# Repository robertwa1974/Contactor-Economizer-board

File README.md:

# Contactor Economizer

A two-channel 12 V economizer board for high-voltage contactor coils, built for an EV conversion using
salvaged contactors.

When the vehicle controller commands a contactor closed, the board pulls it in with a strong,
current-regulated pulse and then holds it at a much lower current. For a Gigavac GV200-005 that cuts the
12 V load from about 28 W to under 1 W per contactor, and the coil runs cool.

**Status:** revision B. The design is complete and the files are ready for JLCPCB, but no board has
been built or tested yet.

## Documentation

- **[Operator's manual](OPERATORS_MANUAL.md)** covers fitting the connectors, wiring, programming, setup,
  bench testing, installation, fault codes and serial commands.
- [Design notes](handoff.md) record the design decisions, calculations, reviews and open items.

## Features

- Two independent channels, commanded directly by the VCU's existing low-side contactor outputs. No VCU
  firmware change is needed.
- Pick-up and hold currents are both regulated, so one board suits coils from 0.5 to 100 Ω.
- Built-in presets for the Gigavac GV200-005, LS Electric GER150 and Panasonic AEV14012. Custom
  settings are entered over a serial port.
- Fail-safe:
  - Only the VCU command can switch a coil on; the microcontroller can only force it off.
  - With no firmware running, the contactors stay open.
- Fast release from a hardware clamp, reverse-polarity protection, and an open-drain status output per
  channel.
- STM32G031 microcontroller, TI TPS1H100-Q1 smart high-side switches, and INA240 current sensing.
- Optional stacking socket for an insulation monitor (IMD) board. The IMD can block a contactor from
  closing but never forces one open. Without an IMD, the board works stand-alone.
- 76 × 66 mm, 2-layer board.

## Repository layout

| Path | Contents |
|---|---|
| `src/main.cpp`, `platformio.ini` | Firmware (PlatformIO, STM32duino) |
| `hw/econ.kicad_pro` | KiCad 10 project: open this to view the schematic and board |
| `hw/econ_schematic.pdf` | Schematic as a PDF |
| `hw/fab/` | JLCPCB order files: Gerber zip, BOM, placement file, 3D renders |
| `hw/design.py` | Parts and connections. The schematic and board are generated from this file. |
| `hw/gen_*.py`, `hw/fab.py` | Generator scripts (see the design notes for the pipeline) |

The schematic and board are generated from `hw/design.py`. Change that file and regenerate, rather
than editing the KiCad files by hand.

## Building the firmware

Open the repository in VS Code with the PlatformIO extension and click **Build**, or run `pio run`.
Flashing and setup are covered in the [operator's manual](OPERATORS_MANUAL.md#5-programming-the-board).

## License

[MIT](LICENSE): this covers the firmware, the hardware design files and the documentation. The board
switches circuits on high-voltage systems. Build and use it at your own risk; the license provides no
warranty.

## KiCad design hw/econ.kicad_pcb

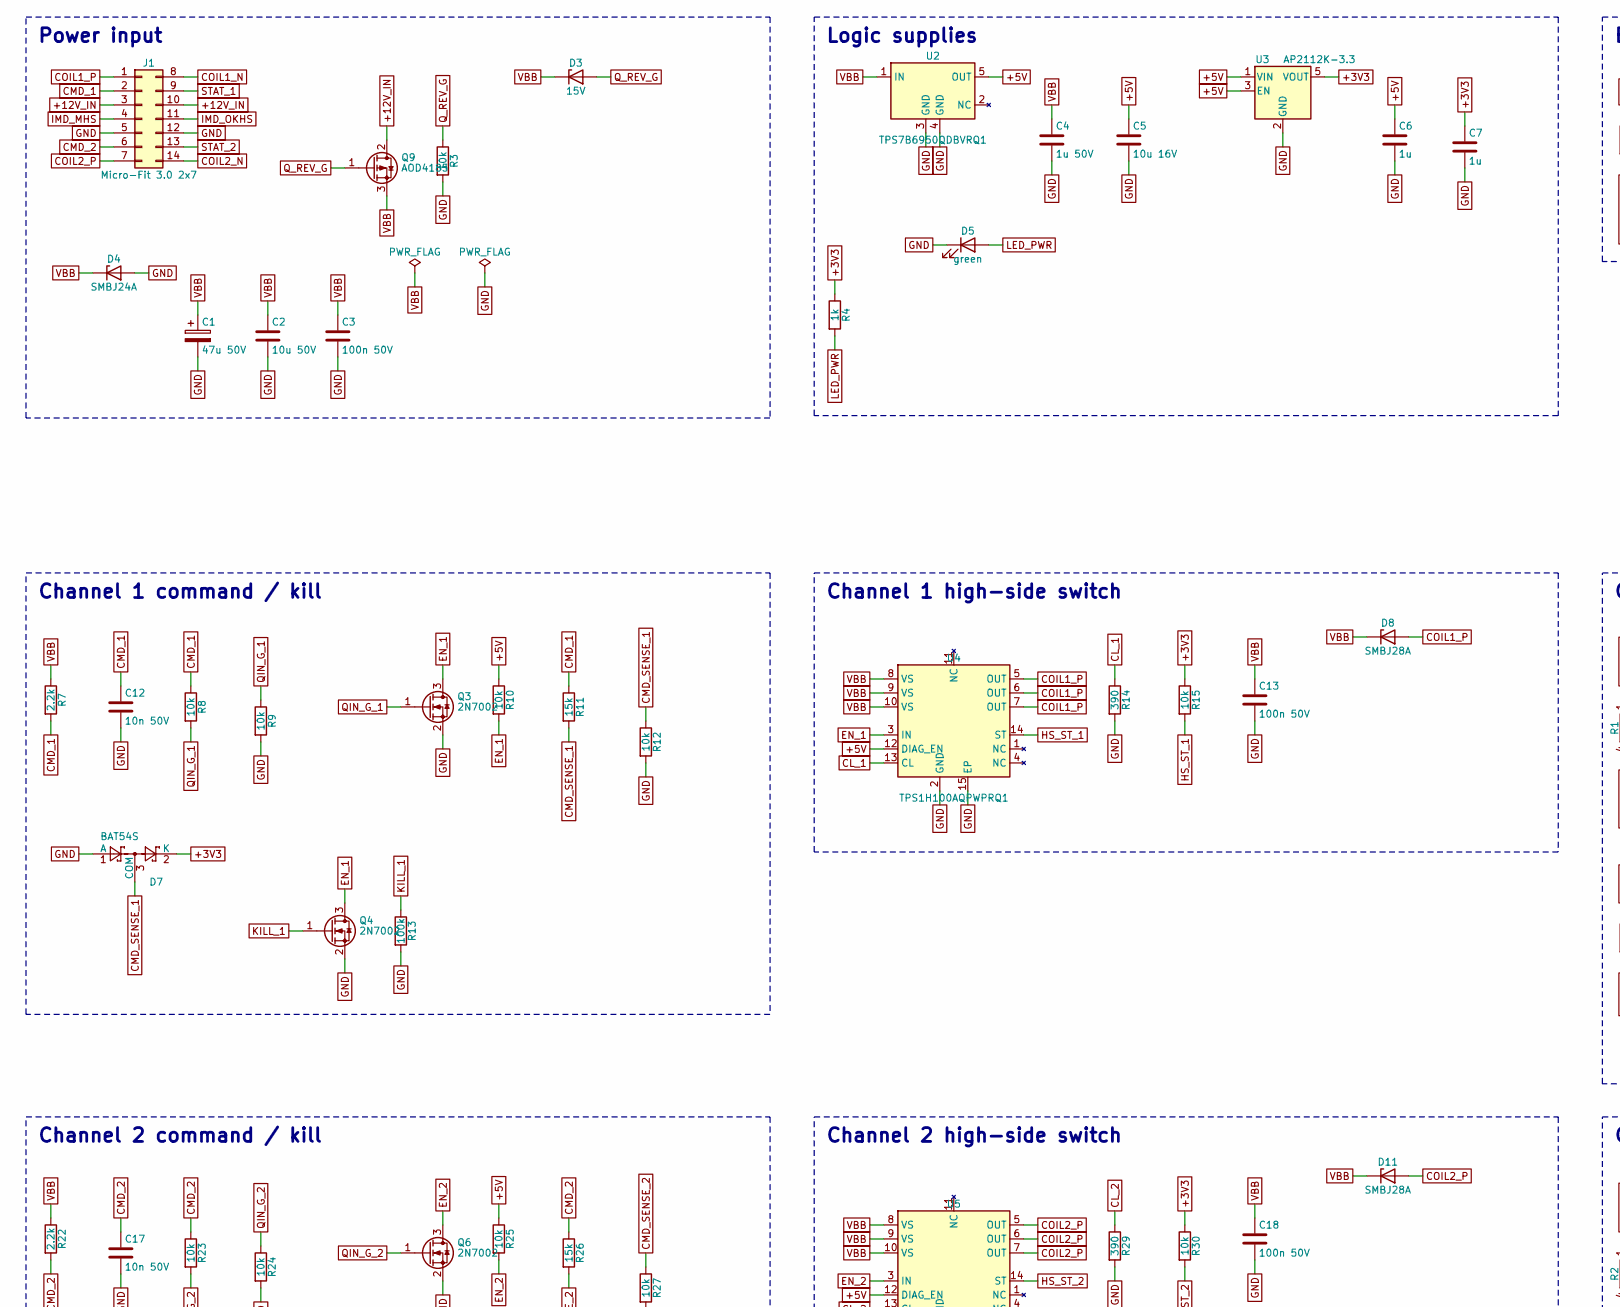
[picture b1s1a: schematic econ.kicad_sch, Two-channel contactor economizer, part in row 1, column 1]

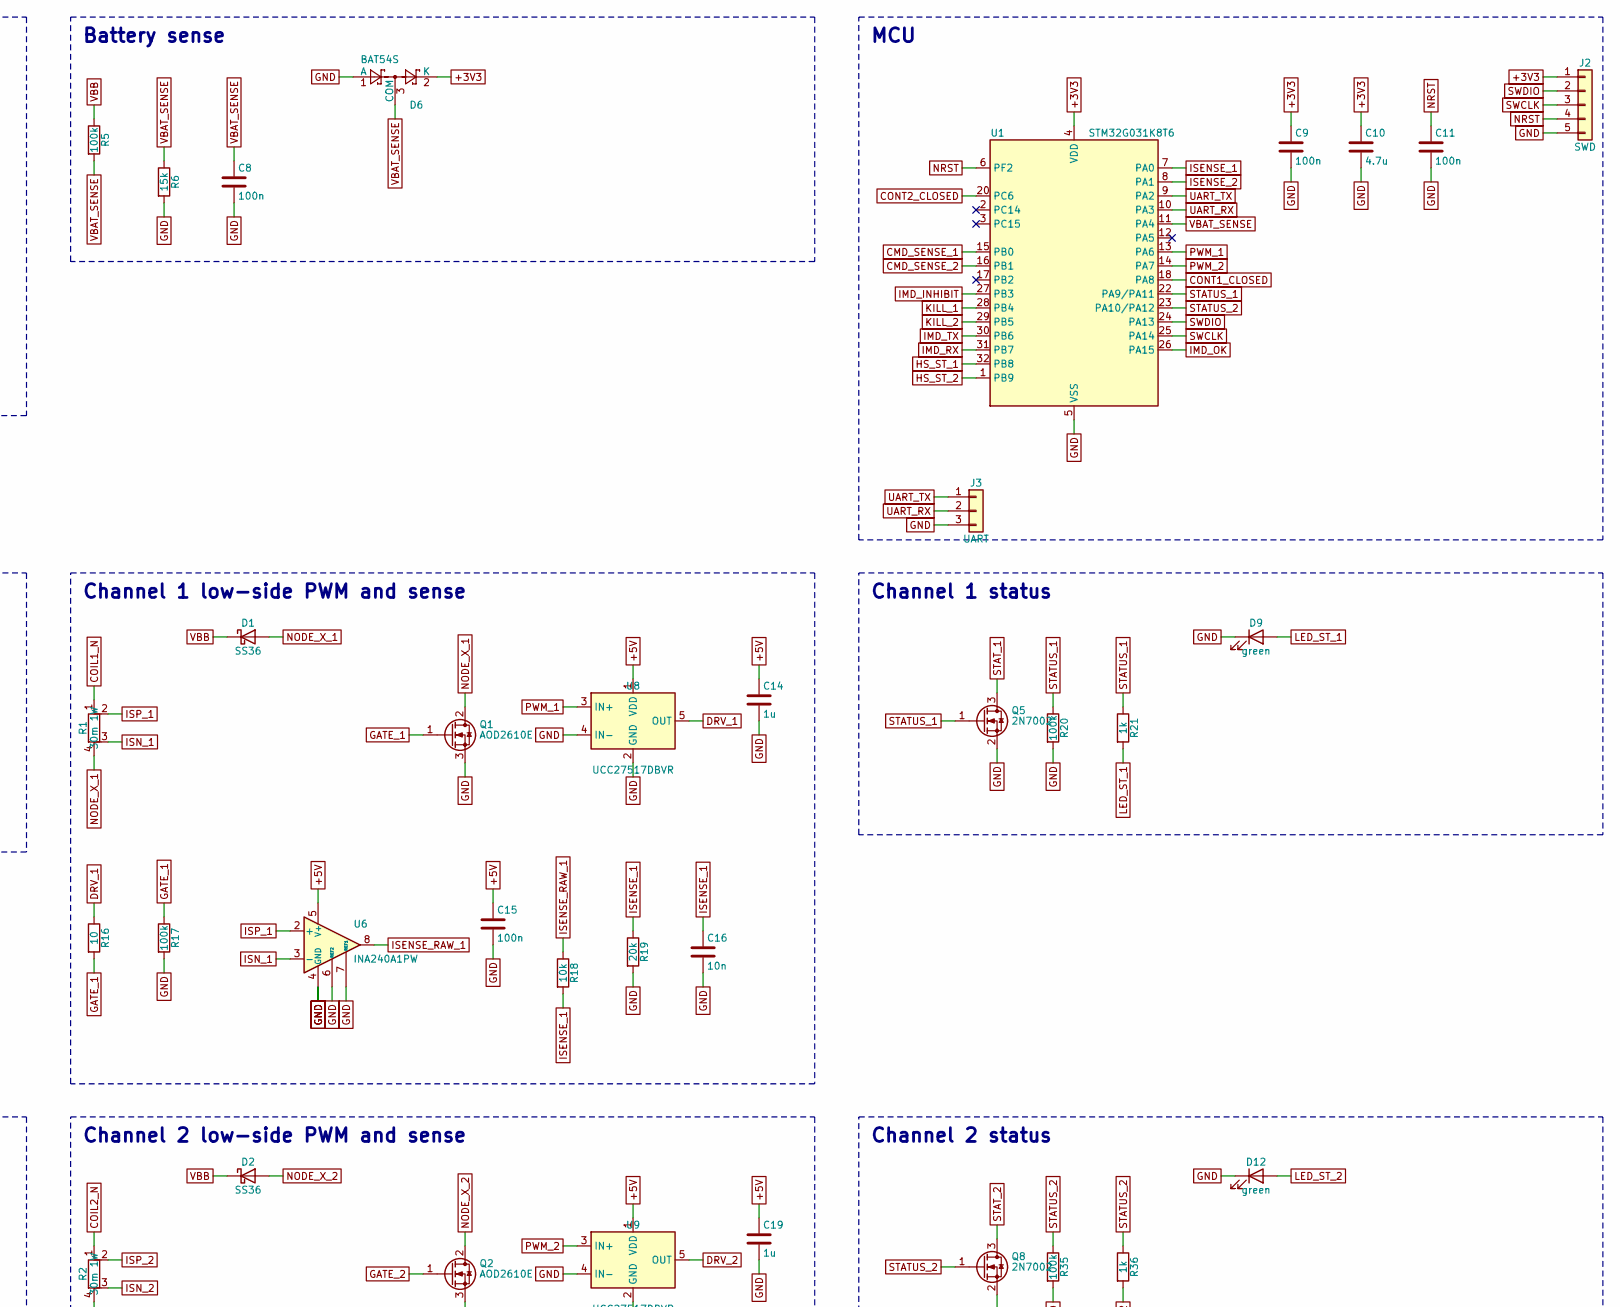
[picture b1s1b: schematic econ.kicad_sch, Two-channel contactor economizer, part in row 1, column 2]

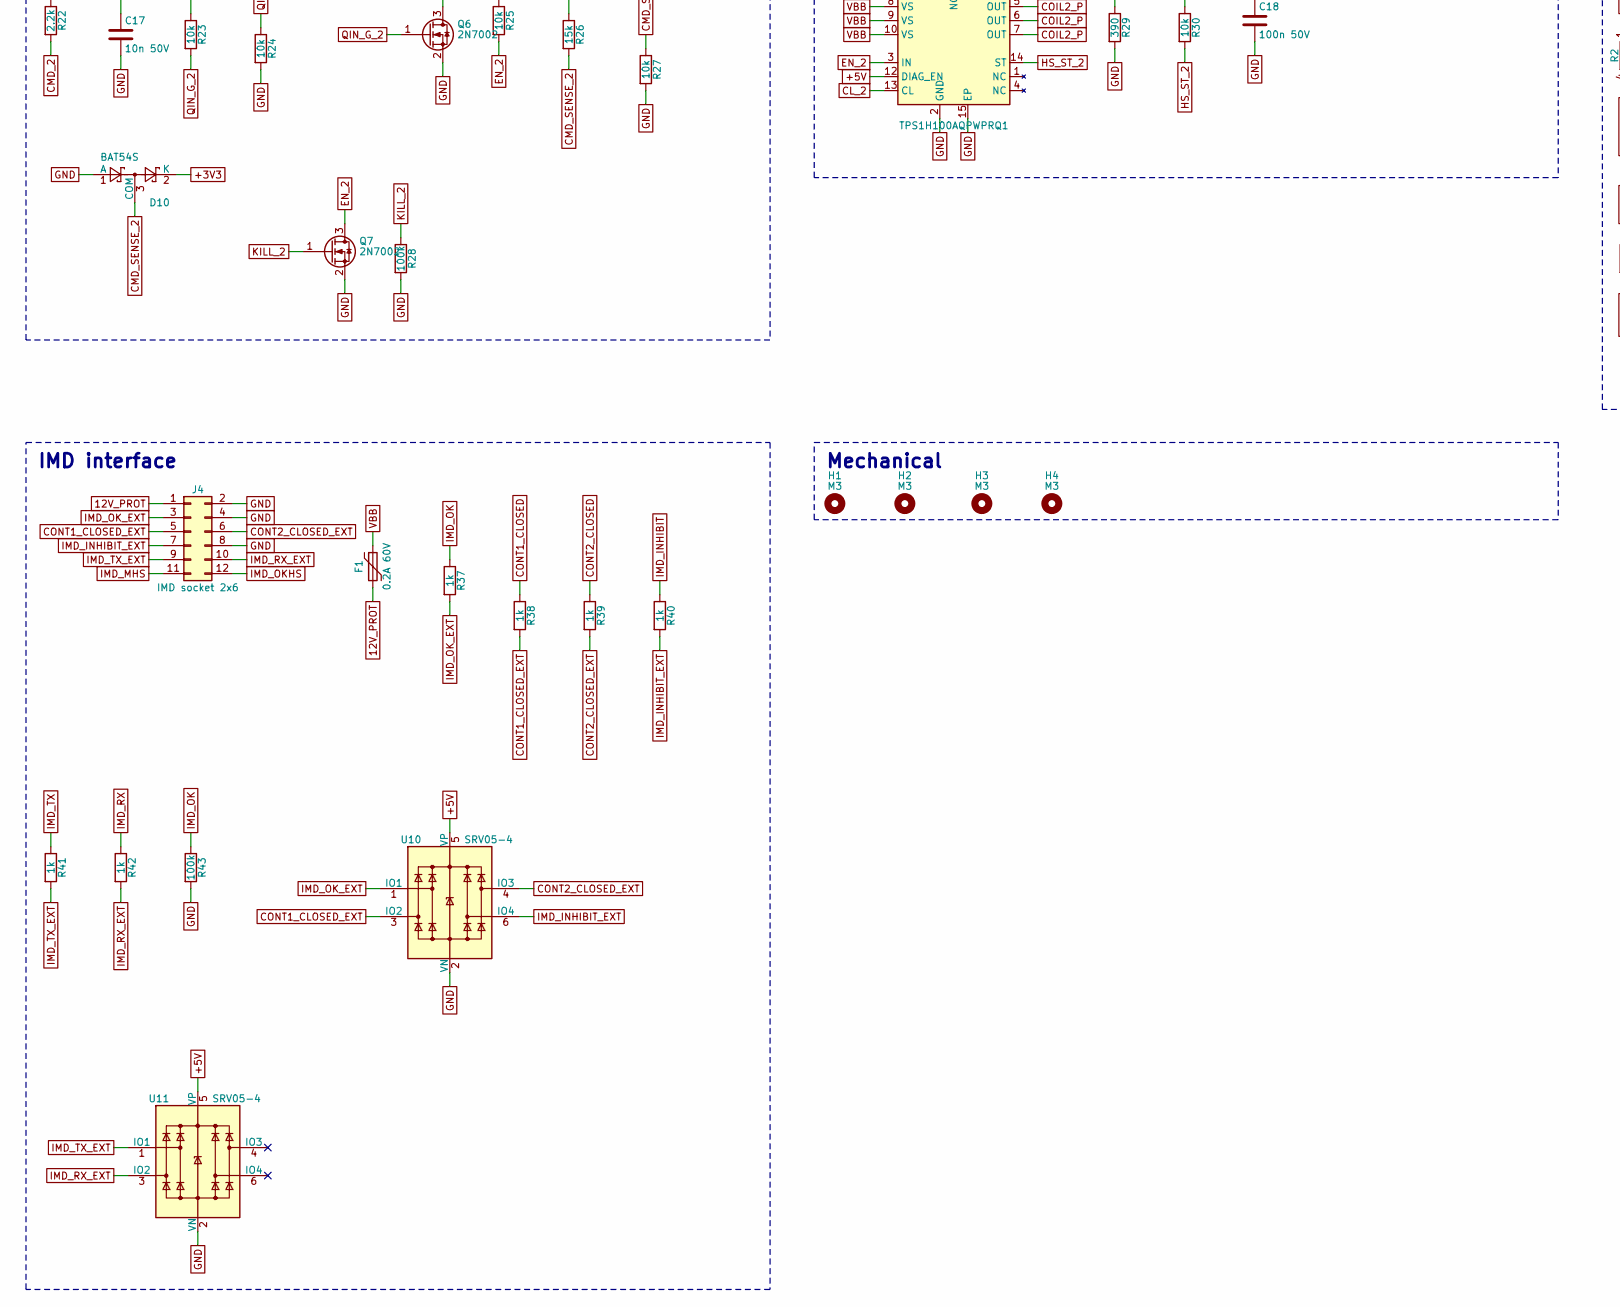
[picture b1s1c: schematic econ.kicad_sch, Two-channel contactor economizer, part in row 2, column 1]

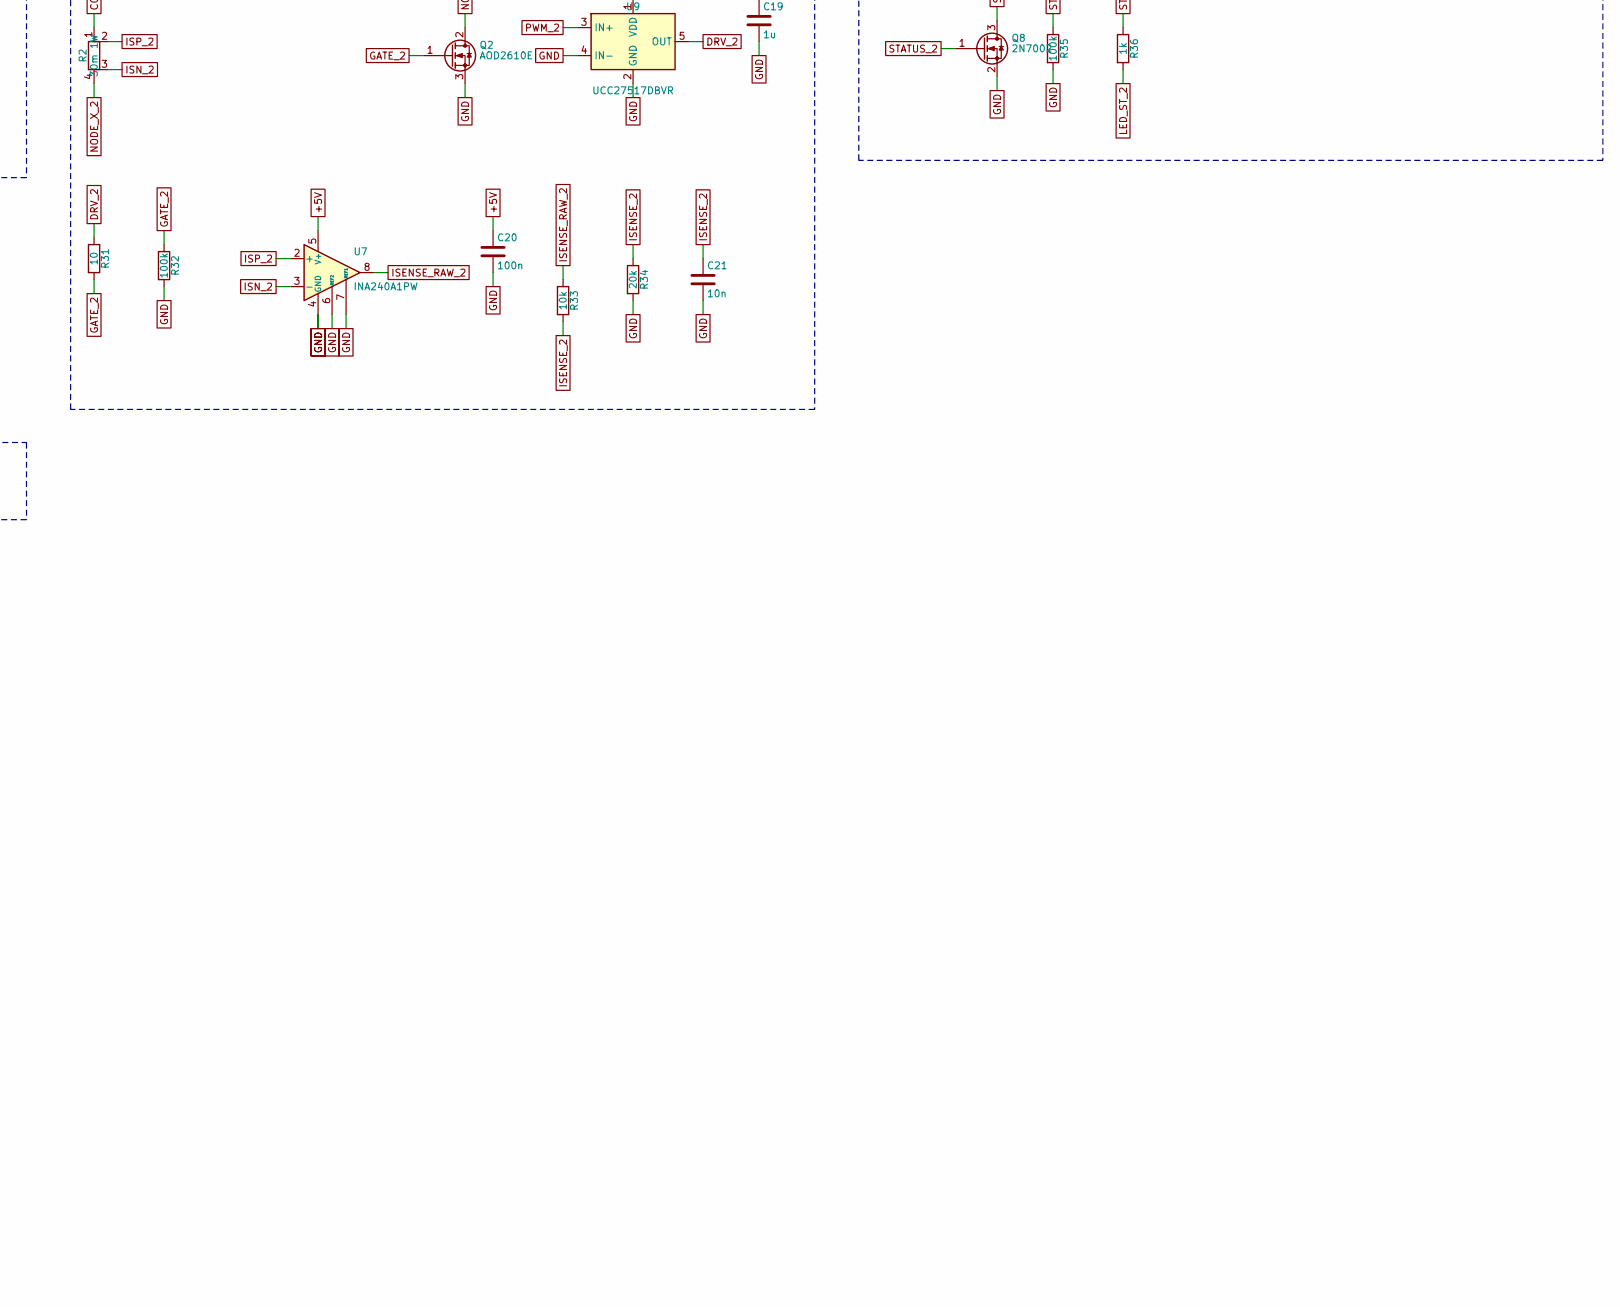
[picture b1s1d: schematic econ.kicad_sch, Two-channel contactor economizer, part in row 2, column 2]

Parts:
C1: 47u 50V; CP_Elec_6.3x7.7
C2: 10u 50V; C_1206_3216Metric
C3, C13, C18: 100n 50V; C_0603_1608Metric
C4: 1u 50V; C_0805_2012Metric
C5: 10u 16V; C_0805_2012Metric
C6, C7, C14, C19: 1u; C_0603_1608Metric
C8, C9, C11, C15, C20: 100n; C_0603_1608Metric
C10: 4.7u; C_0603_1608Metric
C12, C17: 10n 50V; C_0603_1608Metric
C16, C21: 10n; C_0603_1608Metric
D1, D2: SS36; D_SMA; MPN SS36; LCSC C727061
D3: 15V; D_SOD-123; MPN MMSZ5245B (15 V)
D4: SMBJ24A; D_SMB; MPN SMBJ24A; LCSC C224017
D5, D9, D12: green; LED_0603_1608Metric
D6, D7, D10: BAT54S; SOT-23; MPN BAT54S; LCSC C171786
D8, D11: SMBJ28A; D_SMB; MPN SMBJ28A
F1: 0.2A 60V; Fuse_1812_4532Metric; MPN MF-MSMF020/60
H1, H2, H3, H4: M3; MountingHole_3.2mm_M3
J1: Micro-Fit 3.0 2x7; Molex_Micro-Fit_3.0_43045-1400_2x07_P3.00mm_Horizontal; MPN Molex 43045-1400
J2: SWD; PinHeader_1x05_P2.54mm_Horizontal_Edge
J3: UART; PinHeader_1x03_P2.54mm_Horizontal_Edge
J4: IMD socket 2x6; PinSocket_2x06_P2.54mm_Vertical; MPN 2x6 female socket, 2.54 mm, 8.5 mm tall
Q1, Q2: AOD2610E; TO-252-2; MPN AOD2610E; LCSC C282428
Q3, Q4, Q5, Q6, Q7, Q8: 2N7002; SOT-23; MPN 2N7002; LCSC C8545
Q9: AOD4185; TO-252-2; MPN AOD4185; LCSC C400894
R1, R2: 30m 1W; R_2512_Kelvin; MPN RLP25FECR030; LCSC C2930482
R3, R8, R9, R10, R12, R15, R18, R23, R24, R25, R27, R30, R33: 10k; R_0603_1608Metric
R4, R21, R36, R37, R38, R39, R40, R41, R42: 1k; R_0603_1608Metric
R5, R13, R17, R20, R28, R32, R35, R43: 100k; R_0603_1608Metric
R6, R11, R26: 15k; R_0603_1608Metric
R7, R22: 2.2k; R_1206_3216Metric
R14, R29: 390; R_0603_1608Metric
R16, R31: 10; R_0603_1608Metric
R19, R34: 20k; R_0603_1608Metric
U1: STM32G031K8T6; LQFP-32_7x7mm_P0.8mm; MPN STM32G031K8T6; LCSC C432203
U2: TPS7B6950QDBVRQ1; SOT-23-5; MPN TPS7B6950QDBVRQ1; LCSC C132202
U3: AP2112K-3.3; SOT-23-5; MPN AP2112K-3.3TRG1; LCSC C51118
U4, U5: TPS1H100AQPWPRQ1; Texas_HTSSOP-14-1EP_4.4x5mm_P0.65mm_EP3.4x5mm_Mask3.155x3.2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; MPN TPS1H100AQPWPRQ1; LCSC C478465
U6, U7: INA240A1PW; TSSOP-8_4.4x3mm_P0.65mm; MPN INA240A1PWR; LCSC C93965
U8, U9: UCC27517DBVR; SOT-23-5; MPN UCC27517DBVR; LCSC C99395
U10, U11: SRV05-4; SOT-23-6; MPN SRV05-4

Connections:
12V_PROT: F1.2, J4.1
+3V3: C7.1, C9.1, C10.1, D6.2 (K), D7.2 (K), D10.2 (K), J2.1, R4.1, R15.1, R30.1, U1.4 (VDD), U3.5 (VOUT)
+5V: C5.1, C6.1, C14.1, C15.1, C19.1, C20.1, R10.1, R25.1, U2.5 (OUT), U3.1 (VIN), U3.3 (EN), U4.12 (DIAG_EN), U5.12 (DIAG_EN), U6.5 (V+), U7.5 (V+), U8.1 (VDD), U9.1 (VDD), U10.5 (VP), U11.5 (VP)
+12V_IN: J1.3, J1.10, Q9.2 (D)
CL_1: R14.1, U4.13 (CL)
CL_2: R29.1, U5.13 (CL)
CMD_1: C12.1, J1.2, R7.2, R8.1, R11.1
CMD_2: C17.1, J1.6, R22.2, R23.1, R26.1
CMD_SENSE_1: D7.3 (COM), R11.2, R12.1, U1.15 (PB0)
CMD_SENSE_2: D10.3 (COM), R26.2, R27.1, U1.16 (PB1)
COIL1_N: J1.8, R1.1
COIL1_P: D8.2 (A), J1.1, U4.5 (OUT), U4.6 (OUT), U4.7 (OUT)
COIL2_N: J1.14, R2.1
COIL2_P: D11.2 (A), J1.7, U5.5 (OUT), U5.6 (OUT), U5.7 (OUT)
CONT1_CLOSED: R38.1, U1.18 (PA8)
CONT1_CLOSED_EXT: J4.5, R38.2, U10.3 (IO2)
CONT2_CLOSED: R39.1, U1.20 (PC6)
CONT2_CLOSED_EXT: J4.6, R39.2, U10.4 (IO3)
DRV_1: R16.1, U8.5 (OUT)
DRV_2: R31.1, U9.5 (OUT)
EN_1: Q3.3 (D), Q4.3 (D), R10.2, U4.3 (IN)
EN_2: Q6.3 (D), Q7.3 (D), R25.2, U5.3 (IN)
GATE_1: Q1.1 (G), R16.2, R17.1
GATE_2: Q2.1 (G), R31.2, R32.1
GND: C1.2, C2.2, C3.2, C4.2, C5.2, C6.2, C7.2, C8.2, C9.2, C10.2, C11.2, C12.2, C13.2, C14.2, C15.2, C16.2, C17.2, C18.2, C19.2, C20.2, C21.2, D4.2 (A), D5.1 (K), D6.1 (A), D7.1 (A), D9.1 (K), D10.1 (A), D12.1 (K), J1.5, J1.12, J2.5, J3.3, J4.2, J4.4, J4.8, Q1.3 (S), Q2.3 (S), Q3.2 (S), Q4.2 (S), Q5.2 (S), Q6.2 (S), Q7.2 (S), Q8.2 (S), R3.2, R6.2, R9.2, R12.2, R13.2, R14.2, R17.2, R19.2, R20.2, R24.2, R27.2, R28.2, R29.2, R32.2, R34.2, R35.2, R43.2, U1.5 (VSS), U2.3 (GND), U2.4 (GND), U3.2 (GND), U4.2 (GND), U4.15 (EP), U5.2 (GND), U5.15 (EP), U6.1 (GND), U6.4 (GND), U6.6 (REF2), U6.7 (REF1), U7.1 (GND), U7.4 (GND), U7.6 (REF2), U7.7 (REF1), U8.2 (GND), U8.4 (IN-), U9.2 (GND), U9.4 (IN-), U10.2 (VN), U11.2 (VN)
HS_ST_1: R15.2, U1.32 (PB8), U4.14 (ST)
HS_ST_2: R30.2, U1.1 (PB9), U5.14 (ST)
IMD_INHIBIT: R40.1, U1.27 (PB3)
IMD_INHIBIT_EXT: J4.7, R40.2, U10.6 (IO4)
IMD_MHS: J1.4, J4.11
IMD_OK: R37.1, R43.1, U1.26 (PA15)
IMD_OKHS: J1.11, J4.12
IMD_OK_EXT: J4.3, R37.2, U10.1 (IO1)
IMD_RX: R42.1, U1.31 (PB7)
IMD_RX_EXT: J4.10, R42.2, U11.3 (IO2)
IMD_TX: R41.1, U1.30 (PB6)
IMD_TX_EXT: J4.9, R41.2, U11.1 (IO1)
ISENSE_1: C16.1, R18.2, R19.1, U1.7 (PA0)
ISENSE_2: C21.1, R33.2, R34.1, U1.8 (PA1)
ISENSE_RAW_1: R18.1, U6.8
ISENSE_RAW_2: R33.1, U7.8
ISN_1: R1.3, U6.3 (-)
ISN_2: R2.3, U7.3 (-)
ISP_1: R1.2, U6.2 (+)
ISP_2: R2.2, U7.2 (+)
KILL_1: Q4.1 (G), R13.1, U1.28 (PB4)
KILL_2: Q7.1 (G), R28.1, U1.29 (PB5)
LED_PWR: D5.2 (A), R4.2
LED_ST_1: D9.2 (A), R21.2
LED_ST_2: D12.2 (A), R36.2
NODE_X_1: D1.2 (A), Q1.2 (D), R1.4
NODE_X_2: D2.2 (A), Q2.2 (D), R2.4
NRST: C11.1, J2.4, U1.6 (PF2)
PWM_1: U1.13 (PA6), U8.3 (IN+)
PWM_2: U1.14 (PA7), U9.3 (IN+)
QIN_G_1: Q3.1 (G), R8.2, R9.1
QIN_G_2: Q6.1 (G), R23.2, R24.1
Q_REV_G: D3.2 (A), Q9.1 (G), R3.1
STATUS_1: Q5.1 (G), R20.1, R21.1, U1.22 (PA9/PA11)
STATUS_2: Q8.1 (G), R35.1, R36.1, U1.23 (PA10/PA12)
STAT_1: J1.9, Q5.3 (D)
STAT_2: J1.13, Q8.3 (D)
SWCLK: J2.3, U1.25 (PA14)
SWDIO: J2.2, U1.24 (PA13)
UART_RX: J3.2, U1.10 (PA3)
UART_TX: J3.1, U1.9 (PA2)
VBAT_SENSE: C8.1, D6.3 (COM), R5.2, R6.1, U1.11 (PA4)
VBB: C1.1, C2.1, C3.1, C4.1, C13.1, C18.1, D1.1 (K), D2.1 (K), D3.1 (K), D4.1 (K), D8.1 (K), D11.1 (K), F1.1, Q9.3 (S), R5.1, R7.1, R22.1, U2.1 (IN), U4.8 (VS), U4.9 (VS), U4.10 (VS), U5.8 (VS), U5.9 (VS), U5.10 (VS)

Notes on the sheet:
Power input
Logic supplies
Battery sense
MCU
Channel 1 command / kill
Channel 1 high-side switch
Channel 1 low-side PWM and sense
Channel 1 status
Channel 2 command / kill
Channel 2 high-side switch
Channel 2 low-side PWM and sense
Channel 2 status
IMD interface
Mechanical

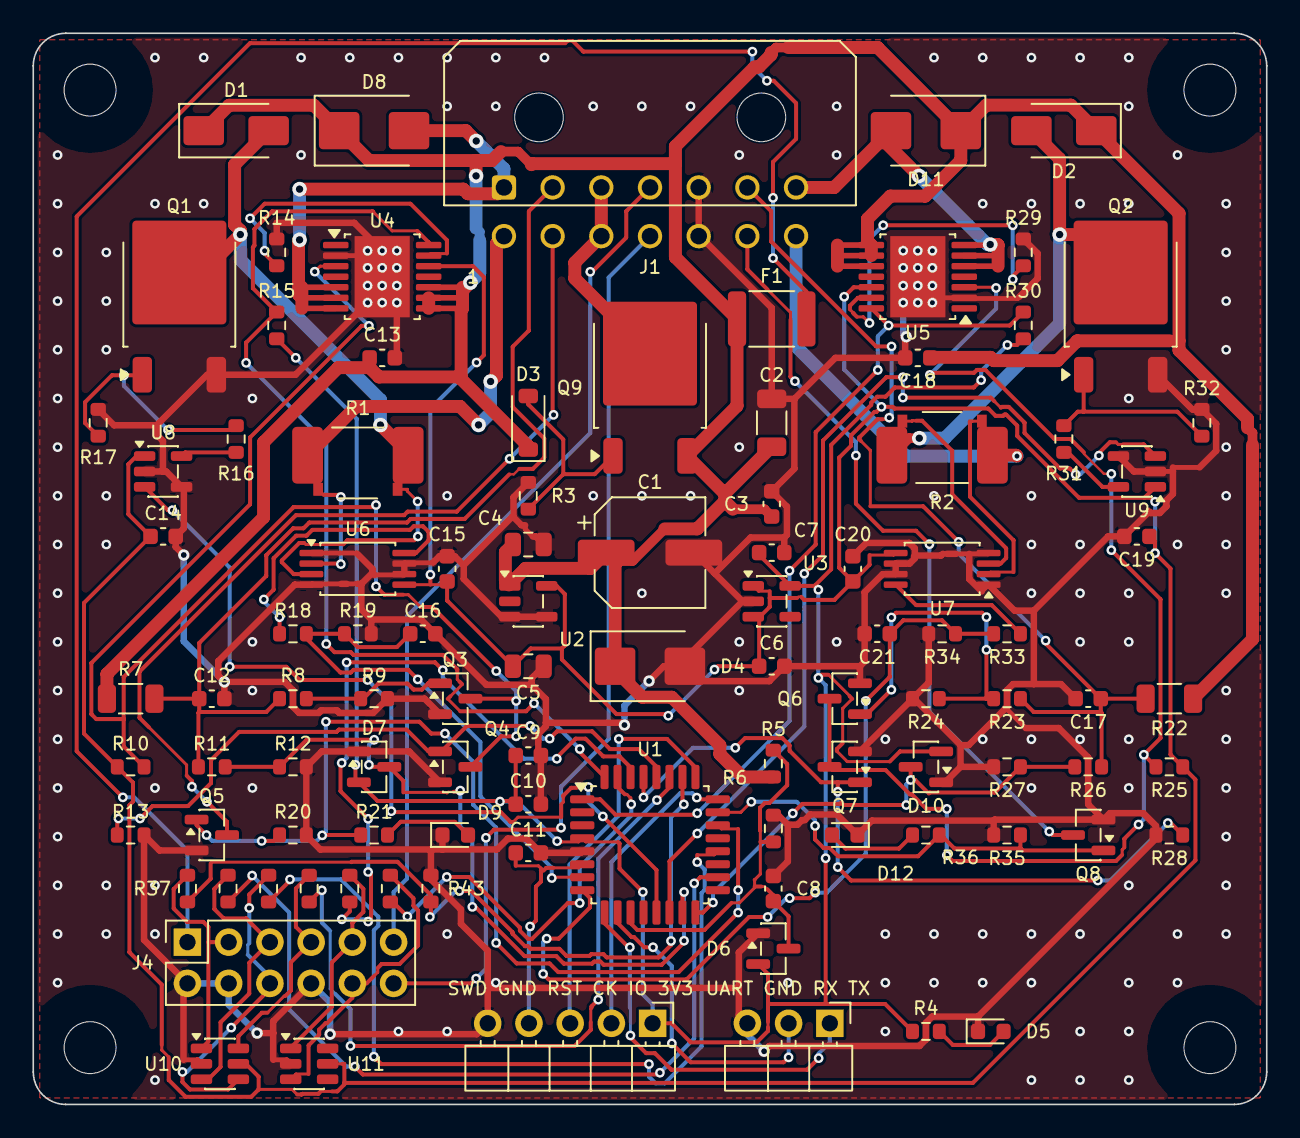
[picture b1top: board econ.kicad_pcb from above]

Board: 2 copper layers, 76.0 x 66.0 mm, 105 parts (0 on the bottom side), 68 nets.

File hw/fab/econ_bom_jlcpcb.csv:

Comment,Designator,Footprint,LCSC Part #,MPN,Qty,Notes
Micro-Fit 3.0 2x7,J1,Molex_Micro-Fit_3.0_43045-1400_2x07_P3.00mm_Horizontal,,Molex 43045-1400,1,"HAND-SOLDER (not in CPL). Not at LCSC: buy from Digi-Key/Mouser, hand-solder"
AOD4185,Q9,TO-252-2,C400894,AOD4185,1,"Reverse-polarity P-FET: drain = input, source = VBB"
10k,"R3,R8,R9,R10,R12,R15,R18,R23,R24,R25,R27,R30,R33",R_0603_1608Metric,,,13,
15V,D3,D_SOD-123,,MMSZ5245B (15 V),1,Q9 gate-source clamp
SMBJ24A,D4,D_SMB,C224017,SMBJ24A,1,TVS1 load-dump clamp (unidirectional)
47u 50V,C1,CP_Elec_6.3x7.7,,,1,"Bulk, damps harness inductance"
10u 50V,C2,C_1206_3216Metric,,,1,
100n 50V,"C3,C13,C18",C_0603_1608Metric,,,3,
TPS7B6950QDBVRQ1,U2,SOT-23-5,C132202,TPS7B6950QDBVRQ1,1,
1u 50V,C4,C_0805_2012Metric,,,1,LDO input
10u 16V,C5,C_0805_2012Metric,,,1,"LDO output, needs >=2.2 uF effective"
AP2112K-3.3,U3,SOT-23-5,C51118,AP2112K-3.3TRG1,1,
1u,"C6,C7,C14,C19",C_0603_1608Metric,,,4,C14: Driver VDD; C19: Driver VDD
1k,"R4,R21,R36,R37,R38,R39,R40,R41,R42",R_0603_1608Metric,,,9,"R37: Series protection, MCU <-> IMD socket; R38: Series protection, MCU <-> IMD socket; R39: Series protection, MCU <-> IMD socket; R40: Series protection, MCU <-> IMD socket; R41: Series protection, MCU <-> IMD socket; R42: Series protection, MCU <-> IMD socket"
green,"D5,D9,D12",LED_0603_1608Metric,,,3,D5: Power LED
100k,"R5,R13,R17,R20,R28,R32,R35,R43",R_0603_1608Metric,,,8,R17: Holds Q off without +5V; R32: Holds Q off without +5V; R43: Missing or dead IMD reads as not OK
15k,"R6,R11,R26",R_0603_1608Metric,,,3,
100n,"C8,C9,C11,C15,C20",C_0603_1608Metric,,,5,
BAT54S,"D6,D7,D10",SOT-23,C171786,BAT54S,3,
STM32G031K8T6,U1,LQFP-32_7x7mm_P0.8mm,C432203,STM32G031K8T6,1,"Pin 22 = PA11, pin 23 = PA12 (default, no remap)"
4.7u,C10,C_0603_1608Metric,,,1,
SWD,J2,PinHeader_1x05_P2.54mm_Horizontal_Edge,,,1,HAND-SOLDER (not in CPL). Right angle. ST-Link: 3V3 SWDIO SWCLK NRST GND
UART,J3,PinHeader_1x03_P2.54mm_Horizontal_Edge,,,1,"HAND-SOLDER (not in CPL). Right angle. 3.3 V USB-serial: board TX, board RX, GND"
2.2k,"R7,R22",R_1206_3216Metric,,,2,Pull-up for VCU low-side output
10n 50V,"C12,C17",C_0603_1608Metric,,,2,Harness noise filter
2N7002,"Q3,Q4,Q5,Q6,Q7,Q8",SOT-23,C8545,2N7002,6,"Q3: Inverts command: VCU low -> EN high; Q4: MCU can force the high side OFF, never ON; Q5: Open drain to VCU: low = holding, no fault; Q6: Inverts command: VCU low -> EN high; Q7: MCU can force the high side OFF, never ON; Q8: Open drain to VCU: low = holding, no fault"
TPS1H100AQPWPRQ1,"U4,U5",Texas_HTSSOP-14-1EP_4.4x5mm_P0.65mm_EP3.4x5mm_Mask3.155x3.255mm,C478465,TPS1H100AQPWPRQ1,2,DIAG_EN high enables ST; CL sets ~6.3 A
390,"R14,R29",R_0603_1608Metric,,,2,I_lim = 1.233 V x 2000 / R = 6.3 A (+/-14%)
SMBJ28A,"D8,D11",D_SMB,,SMBJ28A,2,"Release clamp across U4: K=VBB, A=COIL+. Vbr 31-34 V < 50 V internal clamp"
30m 1W,"R1,R2",R_2512_Kelvin,C2930482,RLP25FECR030,2,Kelvin: sense pads 2/3 net-tied to 1/4
SS36,"D1,D2",D_SMA,C727061,SS36,2,Freewheel to VBB
AOD2610E,"Q1,Q2",TO-252-2,C282428,AOD2610E,2,
UCC27517DBVR,"U8,U9",SOT-23-5,C99395,UCC27517DBVR,2,
10,"R16,R31",R_0603_1608Metric,,,2,
INA240A1PW,"U6,U7",TSSOP-8_4.4x3mm_P0.65mm,C93965,INA240A1PWR,2,
20k,"R19,R34",R_0603_1608Metric,,,2,
10n,"C16,C21",C_0603_1608Metric,,,2,
IMD socket 2x6,J4,PinSocket_2x06_P2.54mm_Vertical,,"2x6 female socket, 2.54 mm, 8.5 mm tall",1,HAND-SOLDER (not in CPL). Hand-solder. Pin 9 = economizer TX (to IMD RX). 11/12 pass straight to J1 4/11
0.2A 60V,F1,Fuse_1812_4532Metric,,MF-MSMF020/60,1,"Bourns PTC: 0.20 A hold, 0.40 A trip, 60 V, 40 A Imax; IMD short cannot blow the harness fuse"
SRV05-4,"U10,U11",SOT-23-6,,SRV05-4,2,U10: ESD on socket logic pins; U11: ESD on socket UART pins

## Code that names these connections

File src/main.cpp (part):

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// IMD (insulation monitor) interface, rev B. IMD_OK must be high this long before
// it counts as OK, so a close during IMD start-up is refused rather than raced.
static const uint32_t IMD_QUALIFY_MS  = 2000;
static const uint32_t IMD_LOST_MS     = 20;     // IMD_OK low this long while closed = warning
// CONTx_CLOSED: coil energised in HOLD/PASS at >= this fraction of hold current.
static const float    CLOSED_FRAC     = 0.60f;
static const uint32_t CLOSED_DEBOUNCE_MS = 20;
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static const float VBAT_V_PER_V   = 15.0f / 115.0f;

// ---------------- Pins ----------------
static const uint32_t PIN_VBAT = PA4;
static const uint32_t PWM_HZ   = 20000;
// IMD stacking socket (J4). USART1 on PB6 (TX, socket pin 9) / PB7 (RX, socket pin 10).
static const uint32_t PIN_IMD_OK      = PA15;  // input, 100k pull-down: high = insulation OK
static const uint32_t PIN_IMD_INHIBIT = PB3;   // output, high = ask the IMD to pause measuring
static const uint32_t IMD_LINK_MS     = 2000;  // no valid frame for this long = link lost (frames every 500 ms)

struct ChannelPins {
  uint32_t isense, pwm, timCh, cmd, kill, hsStatus, status, closed;
};
static const ChannelPins PINS[2] = {
  // HS_ST on PB8/PB9 since rev B (polled; was PB6/PB7).
  { PA0, PA6, 1, PB0, PB4, PB8, PA11, PA8 },
  // PA7's first PinMap_TIM entry is TIM1_CH1N; PA7_ALT1 selects TIM3_CH2 (AF1).
  { PA1, PA7_ALT1, 2, PB1, PB5, PB9, PA12, PC6 },
};

// ---------------- Profiles ----------------
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enum Fault : uint8_t {
  F_NONE = 0, F_PICKUP_LOW = 1, F_OVERCURRENT = 2, F_HOLD_LOW = 4,
  F_HOLD_HIGH = 8, F_HS_SWITCH = 16, F_NOT_CONFIGURED = 32,
  F_IMD_INHIBIT = 64    // close refused: IMD required and IMD_OK not qualified
};

struct Channel {
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static uint32_t pwmTicks = 0;
static float vbat = 12.0f;
static bool logOn = true;
static bool imdOkRaw = false;          // IMD_OK pin level this cycle
static bool imdOkQualified = false;    // high continuously for IMD_QUALIFY_MS
static uint32_t tImdHigh = 0;

// IMD UART link (information only). USART1: Uart(RX, TX) is the STM32 core's concrete serial class.
static Uart imdSerial(PB7, PB6);
static struct {
  imdproto::Frame f;        // last valid frame
  uint32_t lastMs = 0;      // when it arrived
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    pinMode(PINS[n].closed, OUTPUT);
    digitalWrite(PINS[n].closed, LOW);
  }
  pinMode(PIN_IMD_OK, INPUT);          // external 100k pull-down
  pinMode(PIN_IMD_INHIBIT, OUTPUT);
  digitalWrite(PIN_IMD_INHIBIT, LOW);  // reserved: IMD keeps measuring
  analogReadResolution(12);

  pwmTim = new HardwareTimer(TIM3);
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  uint32_t now = millis();

  vbat = readVolts(PIN_VBAT) / VBAT_V_PER_V;
  bool imdNow = (digitalRead(PIN_IMD_OK) == HIGH);
  if (imdNow && !imdOkRaw) tImdHigh = now;
  imdOkRaw = imdNow;
  imdOkQualified = imdNow && (now - tImdHigh >= IMD_QUALIFY_MS);
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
